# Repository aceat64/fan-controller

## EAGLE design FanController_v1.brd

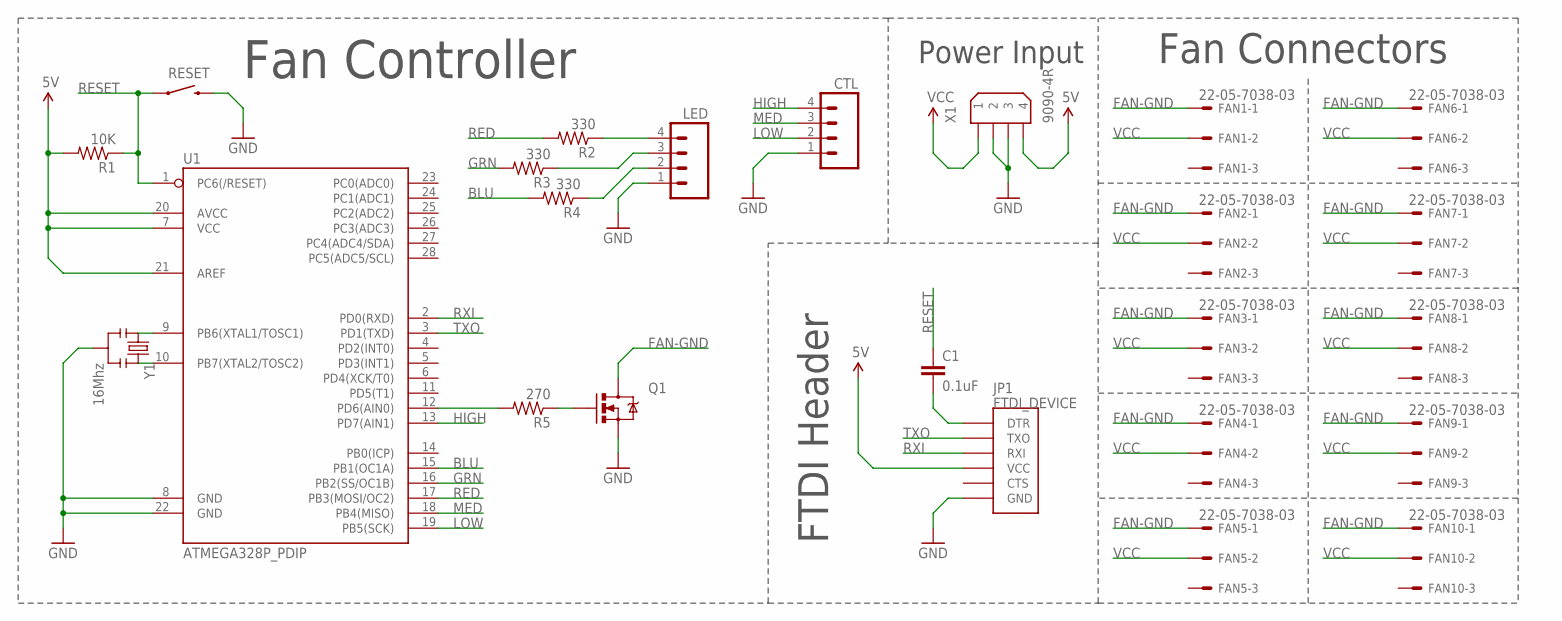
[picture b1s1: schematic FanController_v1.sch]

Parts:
C1: 0.1uF; CAP-PTH-SMALL
CTL: M04PTH; 1X04
FAN1, FAN2, FAN3, FAN4, FAN5, FAN6, FAN7, FAN8, FAN9, FAN10: 22-05-7038-03; 7395-03
JP1: FTDI_DEVICE; FTDI_DEVICE_SIDE
LED: M04PTH; 1X04
Q1: MOSFET-NCHANNELFQP30N06L; TO220V
R1: 10K; AXIAL-0.4
R2, R3, R4: 330; AXIAL-0.4
R5: 270; AXIAL-0.4
RESET: SWITCH-MOMENTARY-2PTH; TACTILE-PTH
U1: ATMEGA328P_PDIP; DIL28-3
X1: 9090-4R
Y1: 16Mhz; RESONATOR-PTH

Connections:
5V: JP1.P$4 (VCC), R1.P$2 (2), U1.7 (VCC), U1.20 (AVCC), U1.21 (AREF), X1.4
BLU: R4.P$2 (2), U1.15 (PB1(OC1A))
FAN-GND: FAN1.1, FAN2.1, FAN3.1, FAN4.1, FAN5.1, FAN6.1, FAN7.1, FAN8.1, FAN9.1, FAN10.1, Q1.2 (D)
GND: CTL.1, JP1.P$6 (GND), LED.1, Q1.3 (S), RESET.3 (2), U1.8 (GND), U1.22 (GND), X1.2, X1.3, Y1.2
GRN: R3.P$2 (2), U1.16 (PB2(SS/OC1B))
HIGH: CTL.4, U1.13 (PD7(AIN1))
LOW: CTL.2, U1.19 (PB5(SCK))
MED: CTL.3, U1.18 (PB4(MISO))
unnamed: U1.10 (PB7(XTAL2/TOSC2)), Y1.3
unnamed: U1.9 (PB6(XTAL1/TOSC1)), Y1.1
unnamed: C1.2, JP1.P$1 (DTR)
unnamed: LED.4, R2.P$1 (1)
unnamed: LED.3, R3.P$1 (1)
unnamed: LED.2, R4.P$1 (1)
unnamed: R5.P$2 (2), U1.12 (PD6(AIN0))
unnamed: Q1.1 (G), R5.P$1 (1)
RED: R2.P$2 (2), U1.17 (PB3(MOSI/OC2))
RESET: C1.1, R1.P$1 (1), RESET.1, U1.1 (PC6(/RESET))
RXI: JP1.P$3 (RXI), U1.2 (PD0(RXD))
TXO: JP1.P$2 (TXO), U1.3 (PD1(TXD))
VCC: FAN1.2, FAN2.2, FAN3.2, FAN4.2, FAN5.2, FAN6.2, FAN7.2, FAN8.2, FAN9.2, FAN10.2, X1.1

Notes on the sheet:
Fan Connectors
Power Input
FTDI Header
Fan Controller

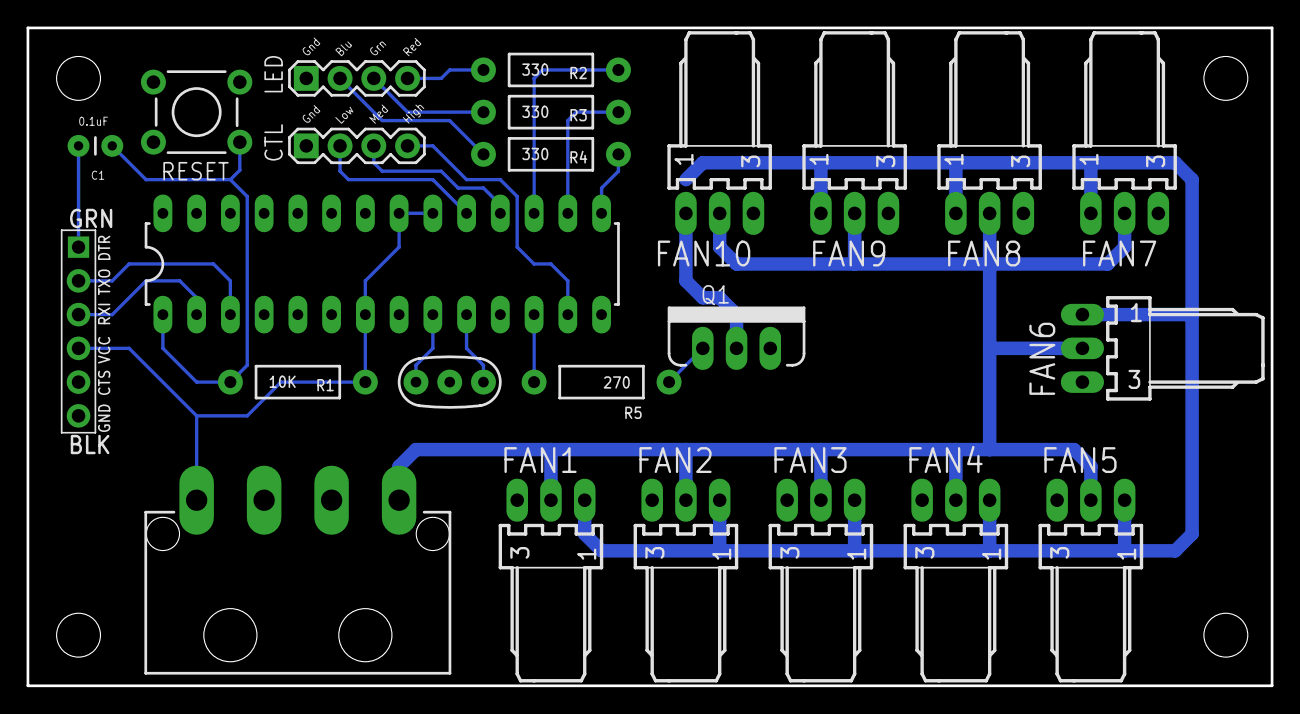
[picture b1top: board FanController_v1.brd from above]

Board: 2 copper layers, 93.7 x 49.5 mm, 28 parts (0 on the bottom side), 21 nets.

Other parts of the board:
U$1, U$2, U$3, U$4: STAND-OFF

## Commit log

2013-05-17 First version (untested)

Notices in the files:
parts and their libraries:
SparkFun-DiscreteSemi: Licensing: CC v3.0 Share-Alike You are welcome to use this library for commercial purposes.
